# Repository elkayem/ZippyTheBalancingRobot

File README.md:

# ZippyTheBalancingRobot

(Click on image above for link to YouTube video)

Zippy 2.0 is a 3D printed Arduino Nano based balancing robot with a custom PCB.  The original prototype version was put together on a breadboard with lots of jumper wires.  This is certainly a great way to get started.  The STMicroelectronics 8A motor drivers do not come in a convenient package for breadboarding, but ST does provide evaluation boards which work well with a prototype system.

The frame can be printed in multiple colors by pausing the print at the right height and switching filament.  The SketchUp 2017 file is included for design customization.  The frame is put together with a few dozen M3x10mm bolts and hex nuts, and four M3 standoffs for the PCB.  I printed the frame in PLA with a 0.2mm layer height and 40% infill.  See more information on the 3D printed frame on [Thingiverse](http://www.thingiverse.com/thing:2291516). 

I've also included an optional set of bumpers, which can protect Zippy in the event of a fall. Wrap the bumpers with pipe insulation tubes for a little extra cushion. Yes, the bumpers detract from Zippy's graceful physique, but make Zippy a little more rugged for kids.

The PCB yields a more compact design than a hand-soldered protoboard, but does require some SMD work and an additional outlay for PCB manufacture.  Even with the fine 0.5 mm pitch, the drivers can be hand soldered to the board (I did!) with a steady hand and patience.  There are plenty of YouTube videos on how to do this.

Here are the important parts for Zippy:
* 2 x VNH5180A motor drivers ($3.72 each as SMD parts, or $8.69 each as evaluation boards from Mouser)
* (Optional) Zippy printed circuit board (see Eagle files) $17.60 from EasyEDA or other PCB maufacturers
* 2 x 30:1 Metal Gearmotor 37Dx68L mm with 64 CPR Encoder ($39.95 each from Pololu)
* GY-521 MPU-6050 gyro/accelerometer breakout board ($4.78 from Amazon)
* Arduino Nano ($2.99 clone from Banggood)
* ZIPPY Flightmax 3000mAh 3S 20C LiPo battery ($22.49 from Amazon)
* 16x2 character LCD display ($5.99 from Amazon)
* Remote control with PWM receiver
* Two Schottky diodes (I used Fairchild SB1245 12A diodes, $1.57 each from Mouser)
* Various resistors, capacitors, 10K trimpot, pushbutton, connectors (see schematic)

I've also included a schematic in the Eagle folder.  Gerber files are provided in the Eagle folder if ordering from a PCB manufacturer.  Otherwise, use a breadboard and wire according to the enclosed schematic.

Pay close attention to polarity on motor wheels (swapping motor leads as necessary) and MPU-6050 orientation.  The software assumes the gyro/accelerometer is mounted with the +X axis facing the front of the robot.  

Depending on your robot inertia, the PID gains may need to be retuned.  Increase as needed to achieve crisp response without any oscillation.  

Also, if you like the colored eyes in [Zippy's video](https://www.youtube.com/watch?v=0io5SwitLzY), I've included the source code for that too.  You need another Arduino Nano or Pro Mini, two RGB LEDs (I used common anode), and six 300 ohm resistors.  The code shows which pins I used.  I just soldered the wires directly to the board, which is attached behind the face plate.  I can control the color, or have a changing rainbow pattern, using my remote control.  I used the left throttle stick on my RC remote.

Here are a few photos:

And a few photos of the prototype V1.0 version:

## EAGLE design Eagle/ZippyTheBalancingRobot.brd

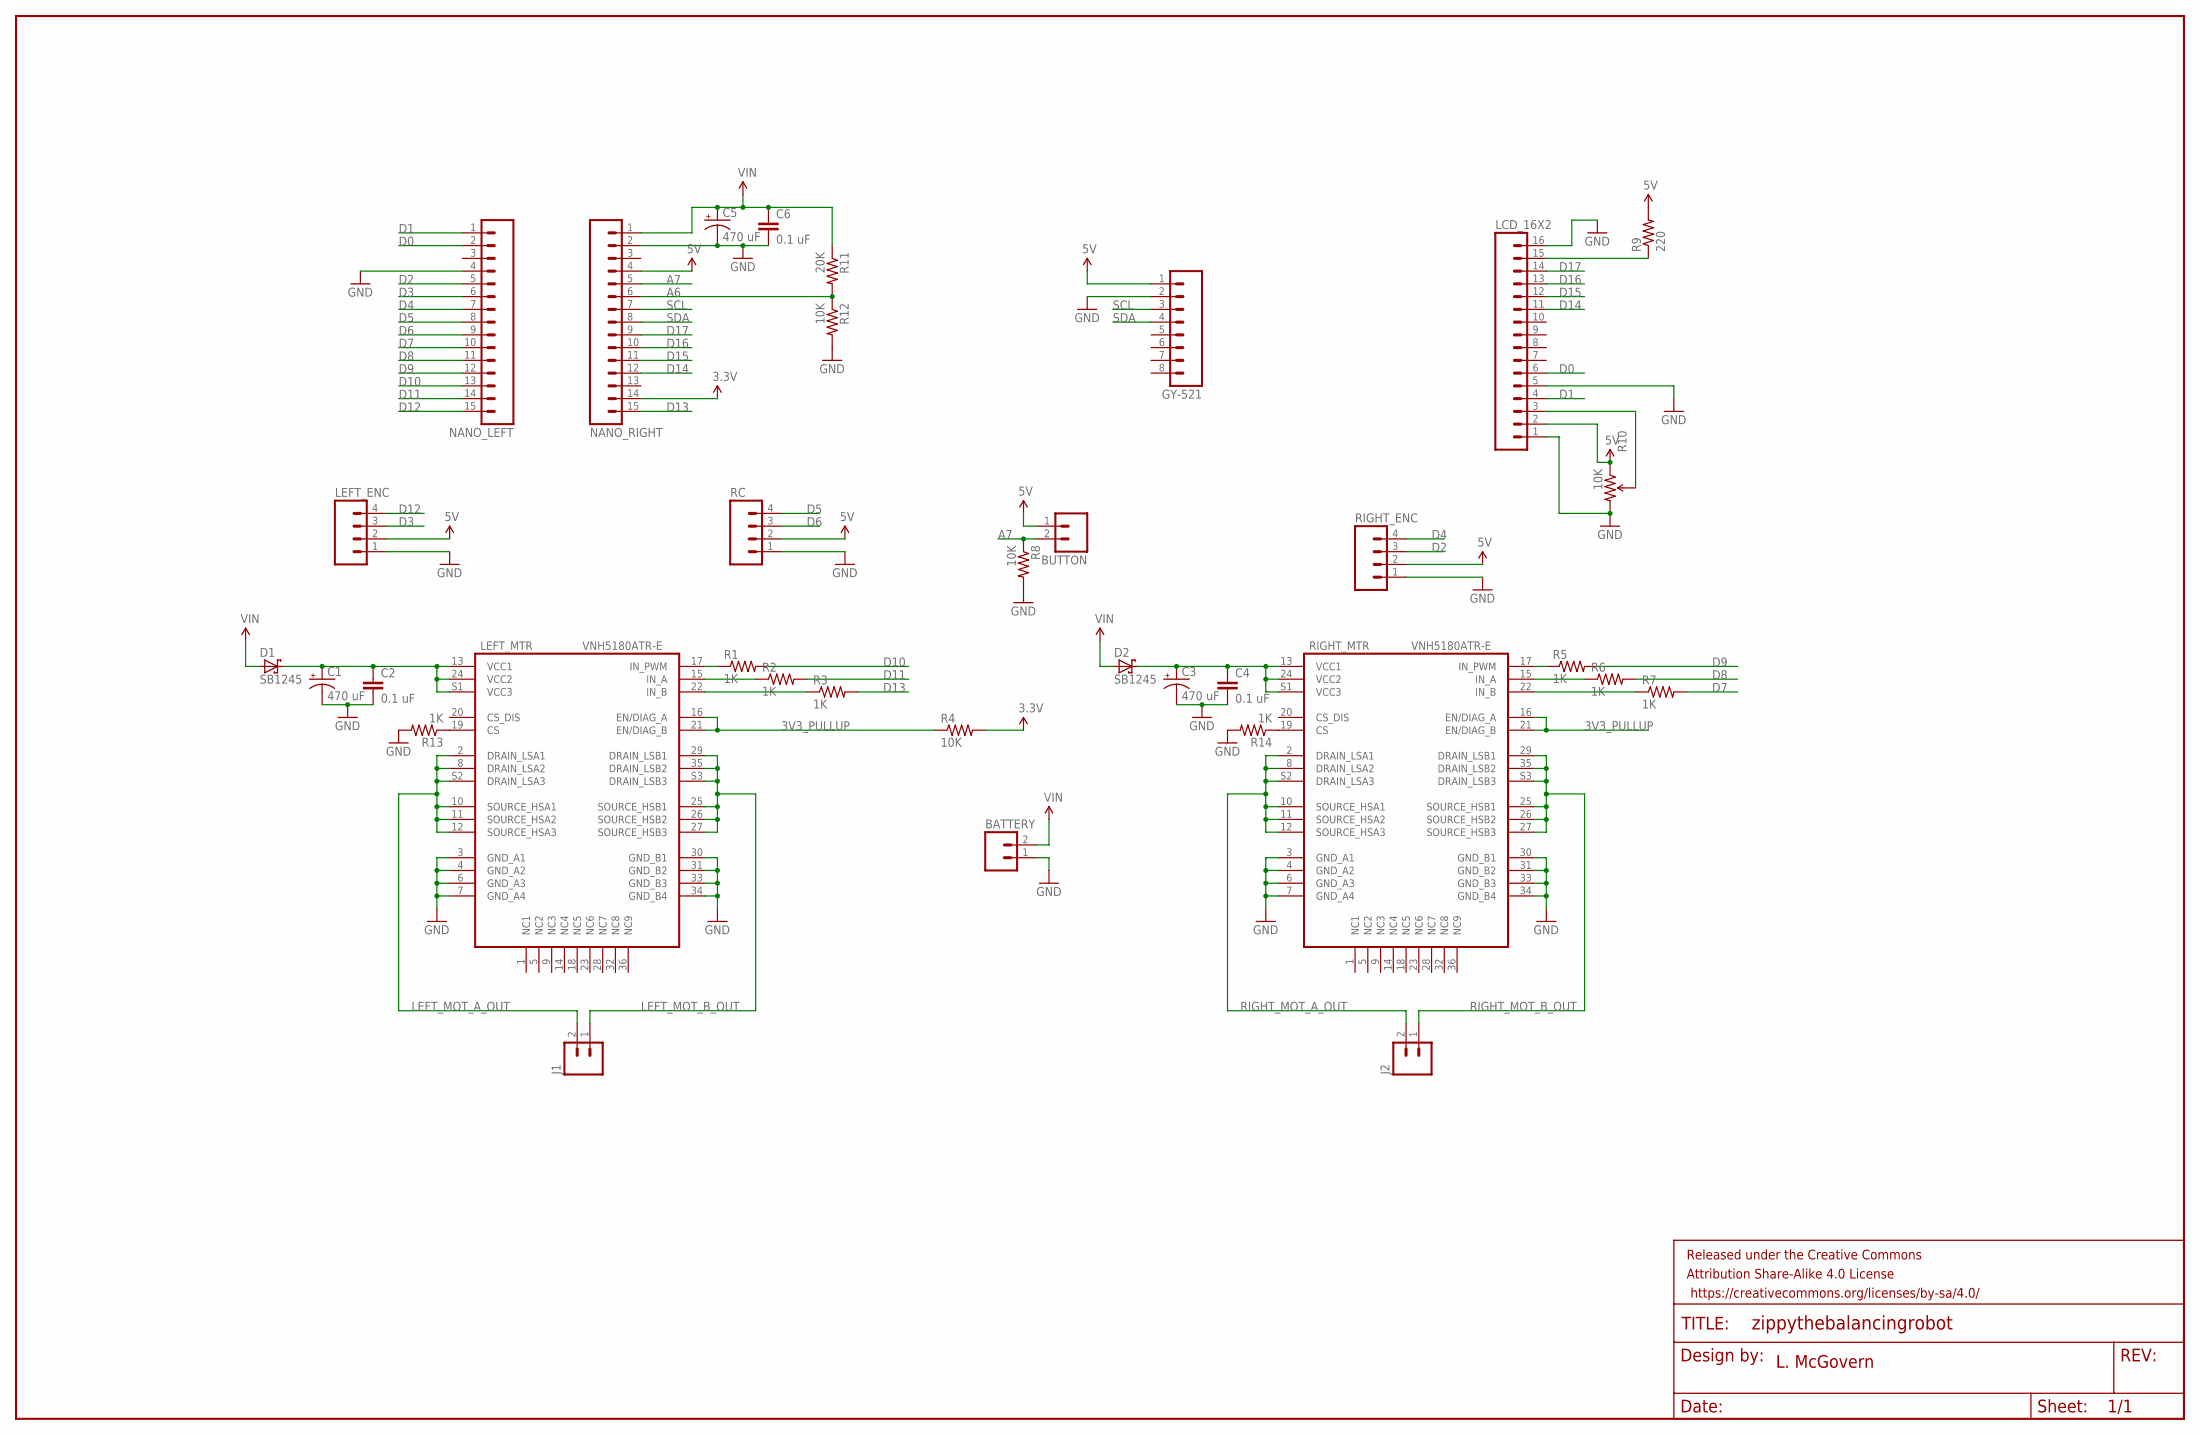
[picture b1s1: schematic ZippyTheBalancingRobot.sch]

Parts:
BATTERY: M025MM; SCREWTERMINAL-5MM-2
BUTTON: M02PTH; 1X02
C1, C3, C5: 470 uF; E3,5-8
C2, C4, C6: 0.1 uF; CAP-PTH-SMALL
D1, D2: SB1245; DO201T15
FRAME1: FRAME-LEDGER; CREATIVE_COMMONS
GY-521: M08; 1X08_ROUND
J1, J2: M025MM; SCREWTERMINAL-5MM-2
LCD_16X2: M16PTH; 1X16
LEFT_ENC: M04PTH; 1X04
LEFT_MTR: VNH5180ATR-E; POWERSSO-36
NANO_LEFT: M15; 1X15
NANO_RIGHT: M15; 1X15
R1, R2, R3, R5, R6, R7, R13, R14: 1K; 0207/10
R4, R8, R12: 10K; 0207/10
R9: 220; 0207/10
R10: 10K; 3386U
R11: 20K; 0207/10
RC: M04PTH; 1X04
RIGHT_ENC: M04PTH; 1X04
RIGHT_MTR: VNH5180ATR-E; POWERSSO-36

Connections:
3.3V: NANO_RIGHT.14, R4.2
3V3_PULLUP: LEFT_MTR.16 (EN/DIAG_A), LEFT_MTR.21 (EN/DIAG_B), R4.1, RIGHT_MTR.16 (EN/DIAG_A), RIGHT_MTR.21 (EN/DIAG_B)
5V: BUTTON.1, GY-521.1, LCD_16X2.2, LEFT_ENC.2, NANO_RIGHT.4, R9.2, R10.1 (CCW), RC.2, RIGHT_ENC.2
A6: NANO_RIGHT.6, R11.2, R12.1
A7: BUTTON.2, NANO_RIGHT.5, R8.1
D0: LCD_16X2.6, NANO_LEFT.2
D1: LCD_16X2.4, NANO_LEFT.1
D2: NANO_LEFT.5, RIGHT_ENC.3
D3: LEFT_ENC.3, NANO_LEFT.6
D4: NANO_LEFT.7, RIGHT_ENC.4
D5: NANO_LEFT.8, RC.4
D6: NANO_LEFT.9, RC.3
D7: NANO_LEFT.10, R7.2
D8: NANO_LEFT.11, R6.2
D9: NANO_LEFT.12, R5.2
D10: NANO_LEFT.13, R1.2
D11: NANO_LEFT.14, R2.2
D12: LEFT_ENC.4, NANO_LEFT.15
D13: NANO_RIGHT.15, R3.2
D14: LCD_16X2.11, NANO_RIGHT.12
D15: LCD_16X2.12, NANO_RIGHT.11
D16: LCD_16X2.13, NANO_RIGHT.10
D17: LCD_16X2.14, NANO_RIGHT.9
GND: BATTERY.1, C1.-, C2.2, C3.-, C4.2, C5.-, C6.2, GY-521.2, LCD_16X2.1, LCD_16X2.5, LCD_16X2.16, LEFT_ENC.1, LEFT_MTR.3 (GND_A1), LEFT_MTR.4 (GND_A2), LEFT_MTR.6 (GND_A3), LEFT_MTR.7 (GND_A4), LEFT_MTR.30 (GND_B1), LEFT_MTR.31 (GND_B2), LEFT_MTR.33 (GND_B3), LEFT_MTR.34 (GND_B4), NANO_LEFT.4, NANO_RIGHT.2, R8.2, R10.3 (CW), R12.2, R13.2, R14.2, RC.1, RIGHT_ENC.1, RIGHT_MTR.3 (GND_A1), RIGHT_MTR.4 (GND_A2), RIGHT_MTR.6 (GND_A3), RIGHT_MTR.7 (GND_A4), RIGHT_MTR.30 (GND_B1), RIGHT_MTR.31 (GND_B2), RIGHT_MTR.33 (GND_B3), RIGHT_MTR.34 (GND_B4)
LED+: LCD_16X2.15, R9.1
LEFT_MOT_A_OUT: J1.2, LEFT_MTR.2 (DRAIN_LSA1), LEFT_MTR.8 (DRAIN_LSA2), LEFT_MTR.10 (SOURCE_HSA1), LEFT_MTR.11 (SOURCE_HSA2), LEFT_MTR.12 (SOURCE_HSA3), LEFT_MTR.S2 (DRAIN_LSA3)
LEFT_MOT_B_OUT: J1.1, LEFT_MTR.25 (SOURCE_HSB1), LEFT_MTR.26 (SOURCE_HSB2), LEFT_MTR.27 (SOURCE_HSB3), LEFT_MTR.29 (DRAIN_LSB1), LEFT_MTR.35 (DRAIN_LSB2), LEFT_MTR.S3 (DRAIN_LSB3)
L_IN_A: LEFT_MTR.15 (IN_A), R2.1
L_IN_B: LEFT_MTR.22 (IN_B), R3.1
L_IN_PWM: LEFT_MTR.17 (IN_PWM), R1.1
unnamed: LEFT_MTR.19 (CS), R13.1
unnamed: R14.1, RIGHT_MTR.19 (CS)
unnamed: C1.+, C2.1, D1.C, LEFT_MTR.13 (VCC1), LEFT_MTR.24 (VCC2), LEFT_MTR.S1 (VCC3)
unnamed: C3.+, C4.1, D2.C, RIGHT_MTR.13 (VCC1), RIGHT_MTR.24 (VCC2), RIGHT_MTR.S1 (VCC3)
RIGHT_MOT_A_OUT: J2.2, RIGHT_MTR.2 (DRAIN_LSA1), RIGHT_MTR.8 (DRAIN_LSA2), RIGHT_MTR.10 (SOURCE_HSA1), RIGHT_MTR.11 (SOURCE_HSA2), RIGHT_MTR.12 (SOURCE_HSA3), RIGHT_MTR.S2 (DRAIN_LSA3)
RIGHT_MOT_B_OUT: J2.1, RIGHT_MTR.25 (SOURCE_HSB1), RIGHT_MTR.26 (SOURCE_HSB2), RIGHT_MTR.27 (SOURCE_HSB3), RIGHT_MTR.29 (DRAIN_LSB1), RIGHT_MTR.35 (DRAIN_LSB2), RIGHT_MTR.S3 (DRAIN_LSB3)
R_IN_A: R6.1, RIGHT_MTR.15 (IN_A)
R_IN_B: R7.1, RIGHT_MTR.22 (IN_B)
R_IN_PWM: R5.1, RIGHT_MTR.17 (IN_PWM)
SCL: GY-521.3, NANO_RIGHT.7
SDA: GY-521.4, NANO_RIGHT.8
V0: LCD_16X2.3, R10.2 (WIPER)
VIN: BATTERY.2, C5.+, C6.1, D1.A, D2.A, NANO_RIGHT.1, R11.1

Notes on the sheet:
L. McGovern

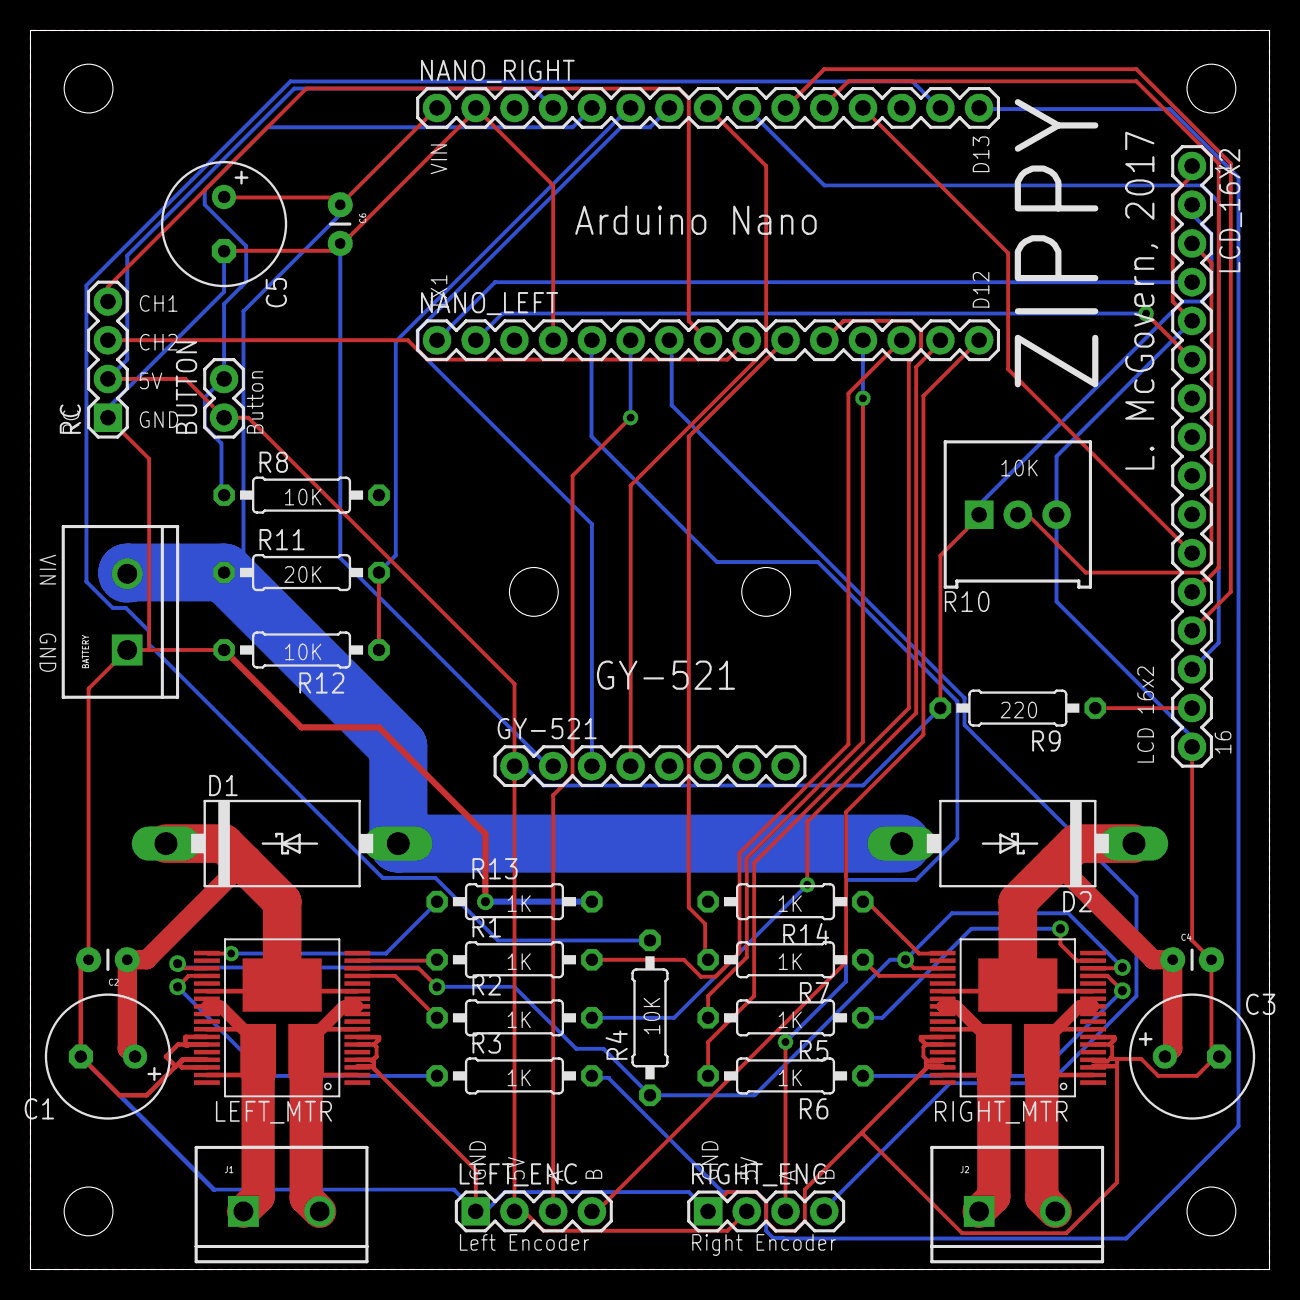
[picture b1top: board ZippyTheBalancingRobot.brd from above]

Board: 2 copper layers, 81.3 x 81.3 mm, 36 parts (0 on the bottom side), 43 nets.

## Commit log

2017-01-08 Checking in code
2017-01-23 Add schematic
2017-01-23 Update schematic
2017-01-26 Add board design
2017-04-02 Update code for PCB, and fix PCB errors.
2017-04-03 Code cleanup and optimization
2017-05-03 Add 3D printer files
2017-05-06 Tweak code for new frame
2017-05-06 Add bumpers
2017-05-07 Added eyes code

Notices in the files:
parts and their libraries:
SparkFun-Aesthetics: Licensing: Creative Commons ShareAlike 4.0 International - https://creativecommons.org/licenses/by-sa/4.0
SparkFun-Aesthetics: Released under the Creative Commons Attribution Share-Alike 4.0 License
SparkFun-Aesthetics: https://creativecommons.org/licenses/by-sa/4.0
